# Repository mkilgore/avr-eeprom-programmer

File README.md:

ATMega328P EEPROM Programmer
============================

This is a simple EEPROM programmer, designed to program the AM29F040B chip.
This project is fully functional at this stage, and includes three distinct
parts:

1. board
  - This is the schematic and PCB layout for the programmer. It uses an
    ATMega328P along with two shift registers to talk to the AM29F040B. It also
    includes a PLCC32 socket for the AM29F040B, a few LEDs for indicating
    read/write, and a serial in/out for talking to the programmer.

1. driver
  - This is the code that runs on the ATMega328P chip and executes the read/write
    commands against the AM29F040B chip.

3. programmer
  - This sends commands to the driver over a serial connection and tells it to
    either read, write, or erase the chip.

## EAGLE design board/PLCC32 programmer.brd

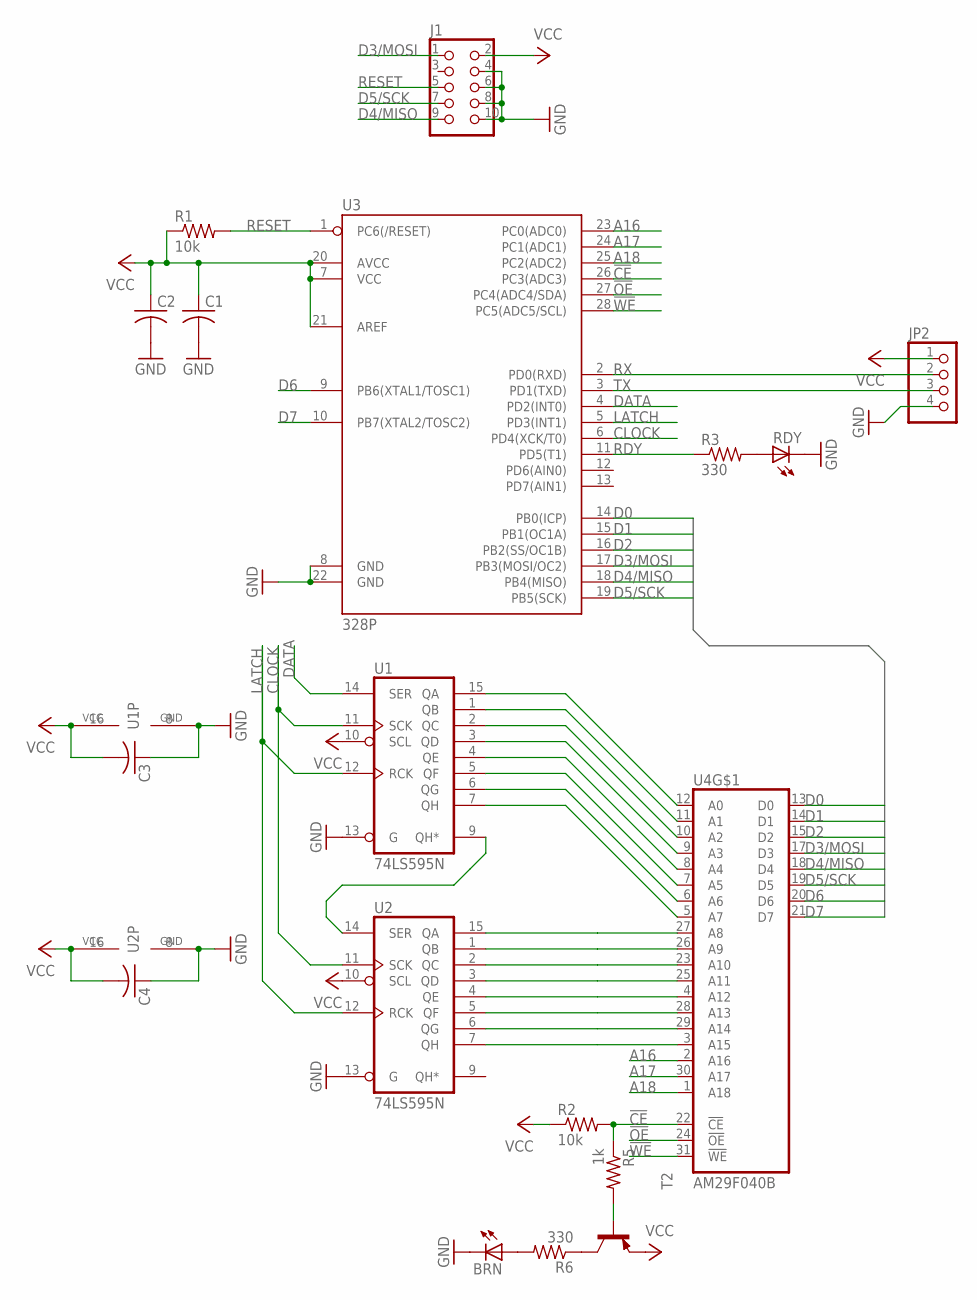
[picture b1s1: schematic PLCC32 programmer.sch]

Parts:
BRN: LED5MM
C1, C2, C3, C4: C-US025-024X044; C025-024X044
J1: CON_HEADER_2X05-PTH+SHROUDED_A; PINSHRD_PTH_2X05
JP2: PINHD-1X4/OCT; 1X04/OCT
R1, R2: 10k; 0204/7
R3, R6: 330; 0204/7
R5: 1k; 0204/7
RDY: LED5MM
T2: BC558A-PNP-TO92-EBC; TO92-EBC
U1, U2: 74LS595N; DIL16
U3: 328P; DIP28
U4: AM29F040B; PLCC-32-SMT-TT

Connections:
!CE: R2.2, R5.1, U3.26 (PC3(ADC3)), U4.22 (!CE)
!OE: U3.27 (PC4(ADC4/SDA)), U4.24 (!OE)
!WE: U3.28 (PC5(ADC5/SCL)), U4.31 (!WE)
A16: U3.23 (PC0(ADC0)), U4.2 (A16)
A17: U3.24 (PC1(ADC1)), U4.30 (A17)
A18: U3.25 (PC2(ADC2)), U4.1 (A18)
CLOCK: U1.11 (SCK), U2.11 (SCK), U3.6 (PD4(XCK/T0))
D0: U3.14 (PB0(ICP)), U4.13 (D0)
D1: U3.15 (PB1(OC1A)), U4.14 (D1)
D2: U3.16 (PB2(SS/OC1B)), U4.15 (D2)
D3/MOSI: J1.1, U3.17 (PB3(MOSI/OC2)), U4.17 (D3)
D4/MISO: J1.9, U3.18 (PB4(MISO)), U4.18 (D4)
D5/SCK: J1.7, U3.19 (PB5(SCK)), U4.19 (D5)
D6: U3.9 (PB6(XTAL1/TOSC1)), U4.20 (D6)
D7: U3.10 (PB7(XTAL2/TOSC2)), U4.21 (D7)
DATA: U1.14 (SER), U3.4 (PD2(INT0))
GND: BRN.K (C), C1.2, C2.2, C3.1, C4.1, J1.4, J1.6, J1.8, J1.10, JP2.4, RDY.K (C), U1.8 (GND), U1.13 (G), U2.8 (GND), U2.13 (G), U3.8 (GND), U3.22 (GND), U4.16 (GND)
LATCH: U1.12 (RCK), U2.12 (RCK), U3.5 (PD3(INT1))
unnamed: U1.9 (QH*), U2.14 (SER)
unnamed: U1.15 (QA), U4.12 (A0)
unnamed: U1.1 (QB), U4.11 (A1)
unnamed: U1.2 (QC), U4.10 (A2)
unnamed: U1.3 (QD), U4.9 (A3)
unnamed: U1.4 (QE), U4.8 (A4)
unnamed: U1.5 (QF), U4.7 (A5)
unnamed: U1.6 (QG), U4.6 (A6)
unnamed: U1.7 (QH), U4.5 (A7)
unnamed: U2.15 (QA), U4.27 (A8)
unnamed: U2.1 (QB), U4.26 (A9)
unnamed: U2.2 (QC), U4.23 (A10)
unnamed: U2.3 (QD), U4.25 (A11)
unnamed: U2.4 (QE), U4.4 (A12)
unnamed: U2.5 (QF), U4.28 (A13)
unnamed: U2.6 (QG), U4.29 (A14)
unnamed: U2.7 (QH), U4.3 (A15)
unnamed: R3.2, RDY.A
unnamed: R6.1, T2.C
unnamed: BRN.A, R6.2
unnamed: R5.2, T2.B
RDY: R3.1, U3.11 (PD5(T1))
RESET: J1.5, R1.2, U3.1 (PC6(/RESET))
RX: JP2.2, U3.2 (PD0(RXD))
TX: JP2.3, U3.3 (PD1(TXD))
VCC: C1.1, C2.1, C3.2, C4.2, J1.2, JP2.1, R1.1, R2.1, T2.E, U1.10 (SCL), U1.16 (VCC), U2.10 (SCL), U2.16 (VCC), U3.7 (VCC), U3.20 (AVCC), U3.21 (AREF), U4.32 (VCC)

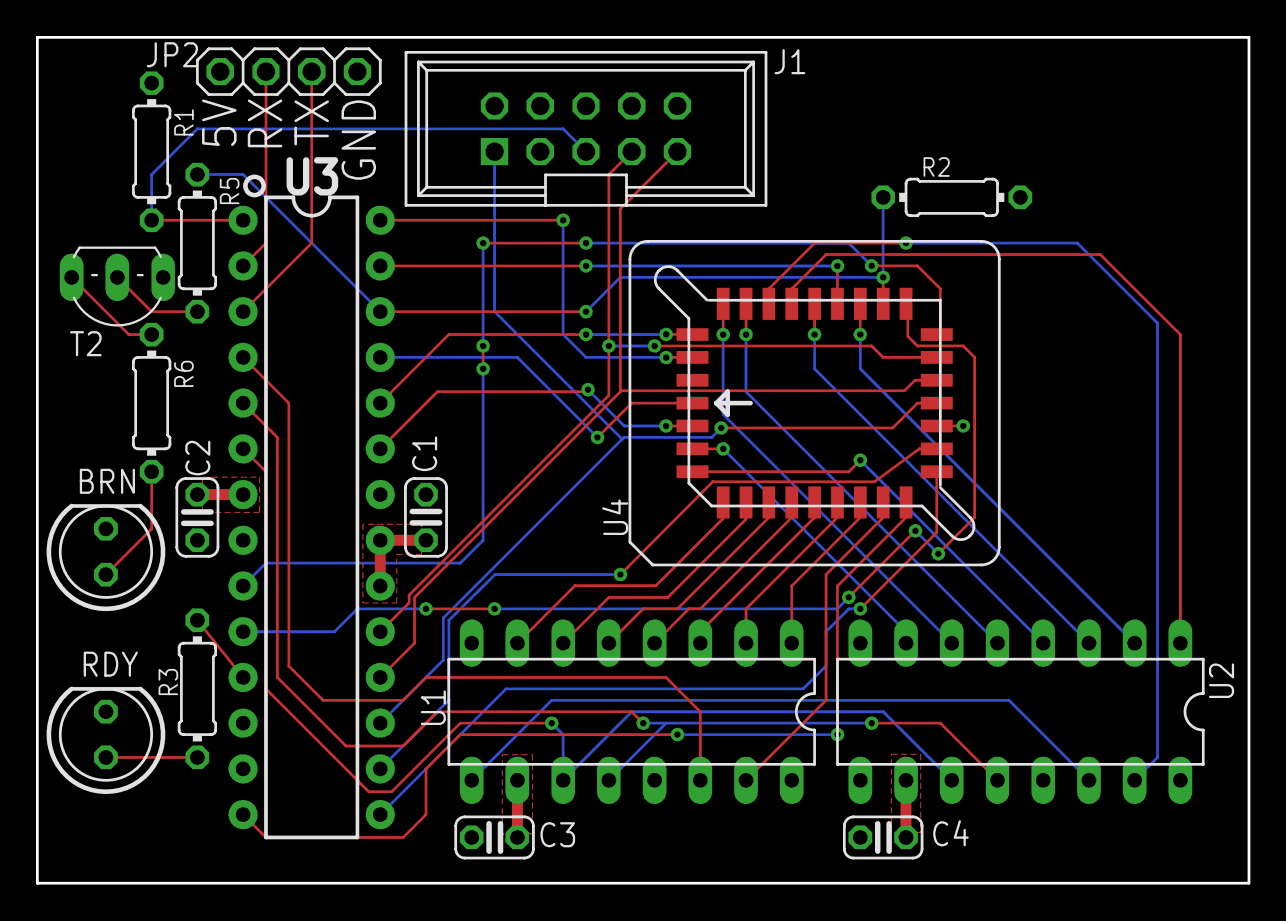
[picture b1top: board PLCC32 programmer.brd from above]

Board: 2 copper layers, 67.3 x 47.0 mm, 18 parts (0 on the bottom side), 44 nets.

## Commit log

2018-09-30 Initial code for EEPROM programmer and driver
2019-12-06 Fix up programmer code
2019-12-06 driver improvements
2019-12-06 add board sch and brd files
2019-12-06 add README.md

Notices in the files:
parts and their libraries:
SparkFun-IC-Microcontroller: Licensing: Creative Commons ShareAlike 4.0 International - https://creativecommons.org/licenses/by-sa/4.0
